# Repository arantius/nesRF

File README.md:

nesRF is a project to retrofit wireless capability into otherwise standard
NES and SNES video game controllers.  It is both hardware (schematic and PCB)
and software (running on an ATMega microcontroller).

The primary goals are:

* Clean design.  External appearance should be minimal, with few visible
  changes from the original stock hardware, besides removing the wire.
* Cross-compatibility: especially, the SNES controller will co-operate with
  either the SNES or NES receiver.

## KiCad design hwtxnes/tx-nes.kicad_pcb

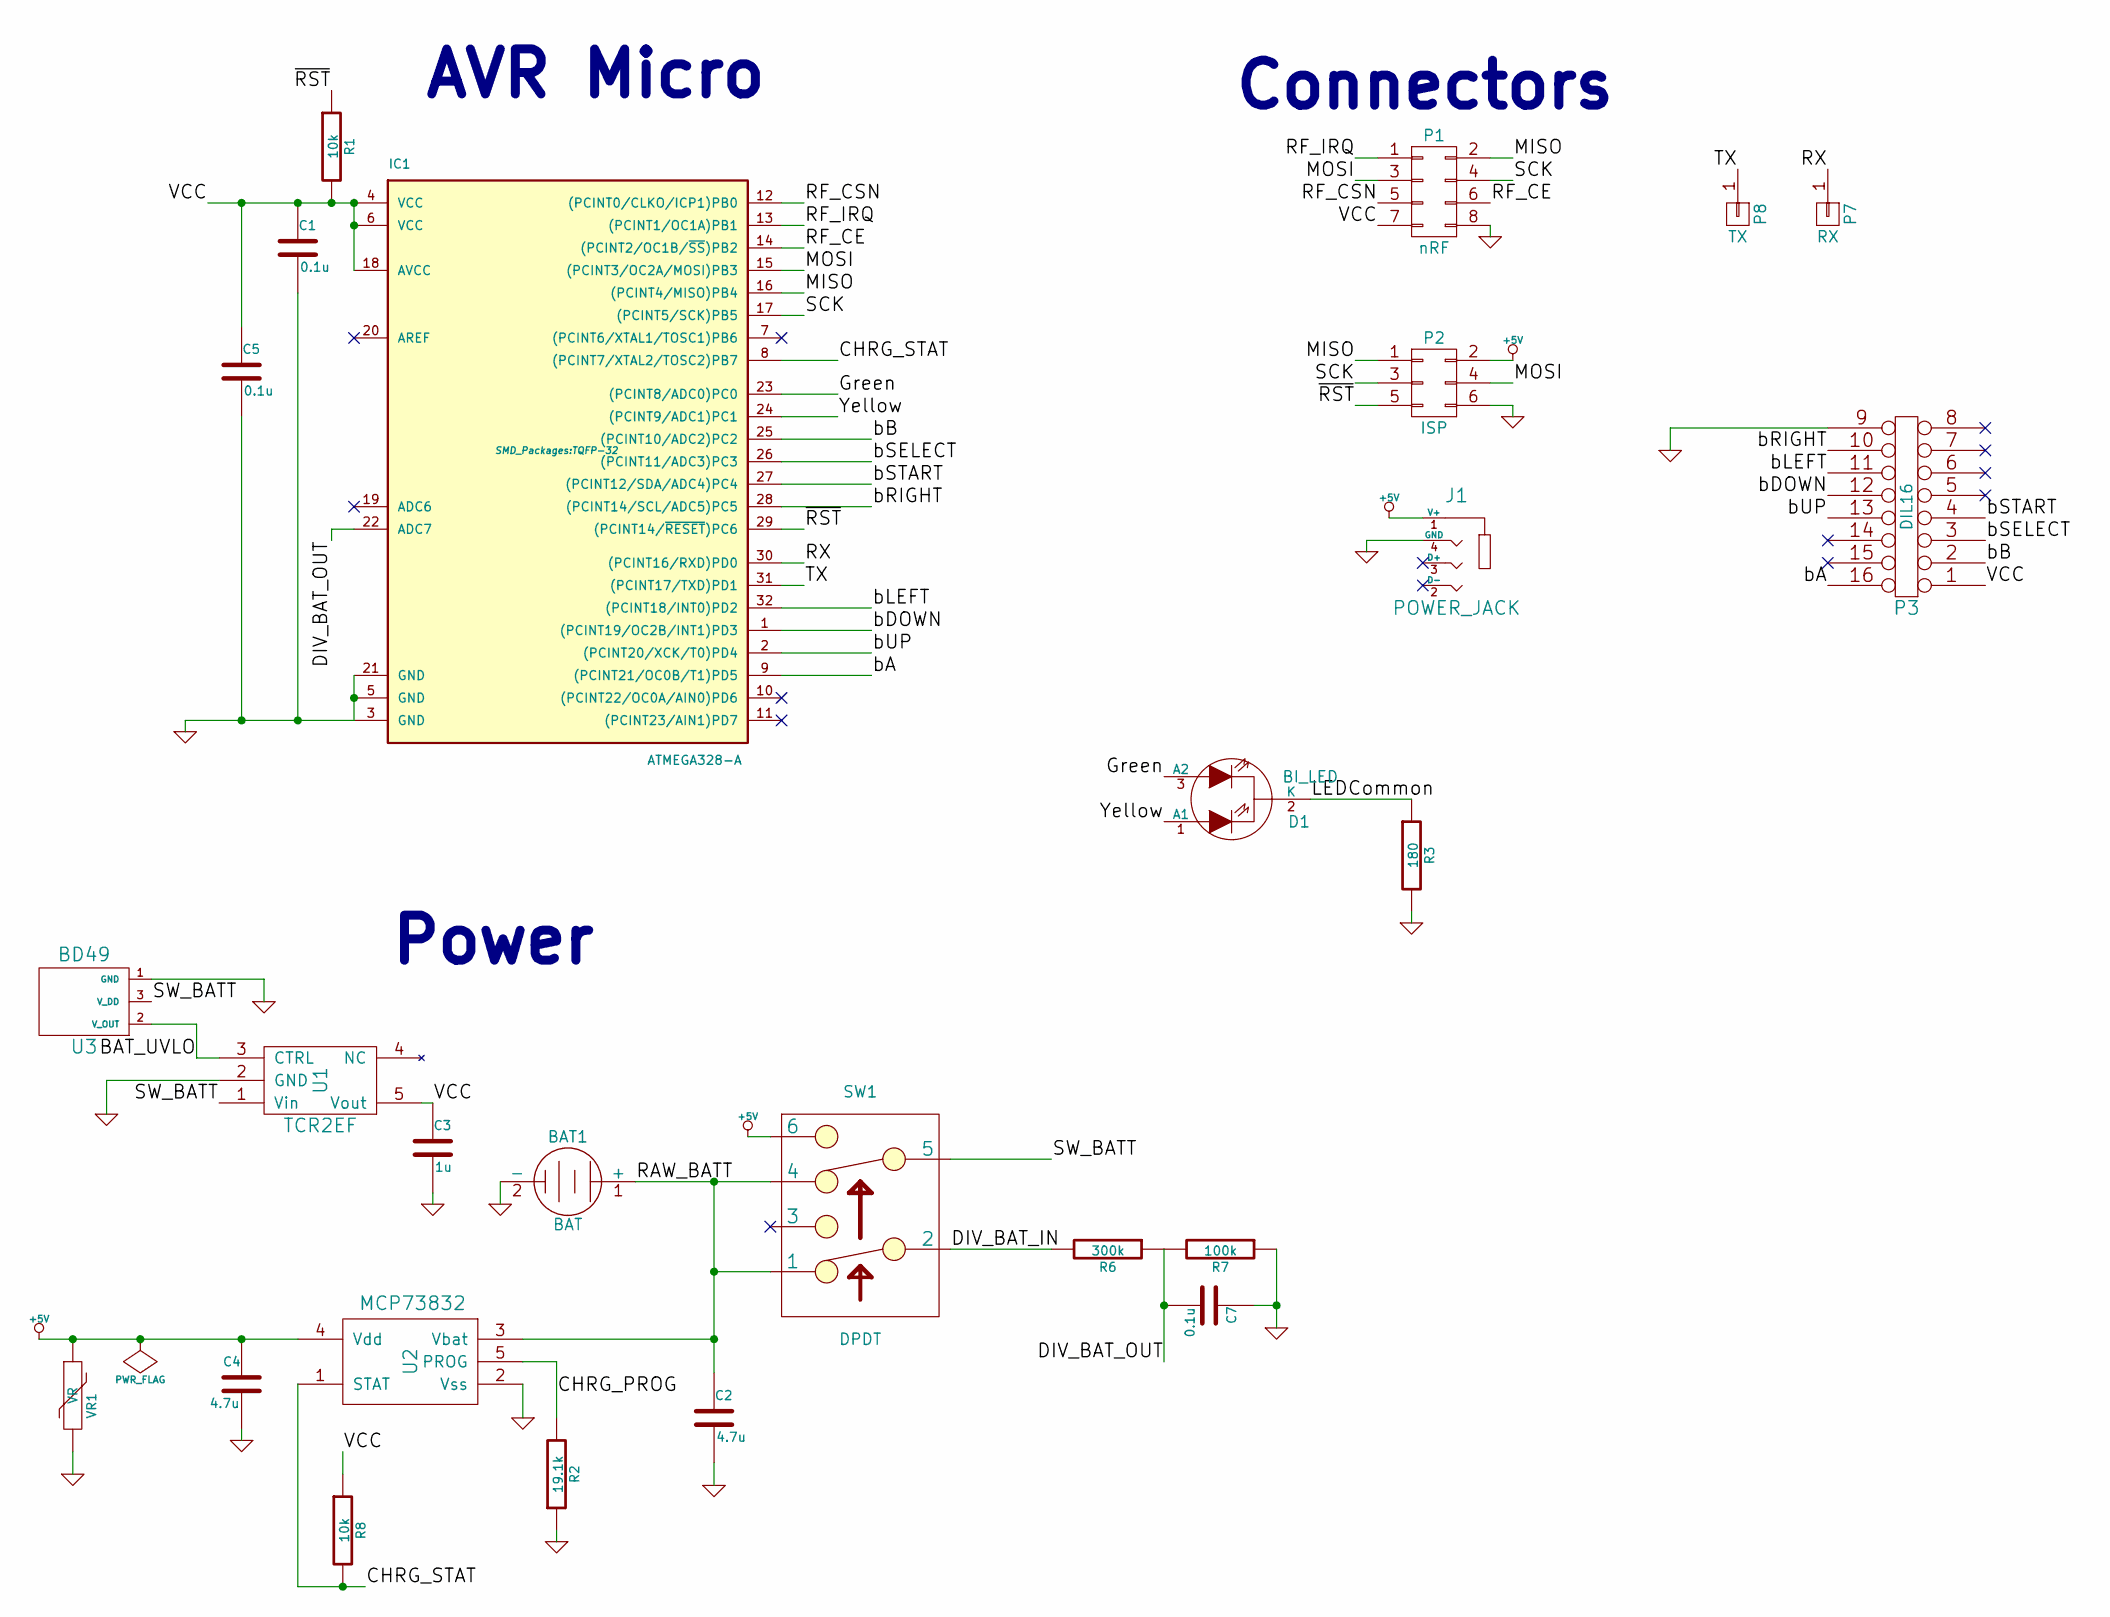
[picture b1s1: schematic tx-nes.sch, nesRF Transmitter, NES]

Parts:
BAT1: BAT; PINHEAD1-2
C1, C5, C7: 0.1u; C_0402
C2, C4: 4.7u; C_0402
C3: 1u; C_0402
D1: BI_LED; Pin_Header_Straight_1x03
IC1: ATMEGA328-A; TQFP-32
J1: POWER_JACK; SJ-4351x
P1: nRF; nRF_Header_2x04
P2: ISP; ISP_POGO
P3: DIL16; NES_PCB_INTERCONNECT
P7: RX; SolderWirePad_single_0-8mmDrill
P8: TX; SolderWirePad_single_0-8mmDrill
R1, R8: 10k; R_0402
R2: 19.1k; R_0402
R3: 180; R_0402
R6: 300k; R_0402
R7: 100k; R_0402
SW1: DPDT; SK22D01
U1: TCR2EF; SOT23-5
U2: MCP73832; SOT23-5
U3: BD49; SSOP-3
VR1: VR; SMD-0603

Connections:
+5V: C4.1, J1.1 (V+), P2.2, SW1.6, U2.4 (Vdd), VR1.1
/BAT_UVLO: U1.3 (CTRL), U3.2 (V_OUT)
/CHRG_PROG: R2.2, U2.5 (PROG)
/CHRG_STAT: IC1.8 ((PCINT7/XTAL2/TOSC2)PB7), R8.2, U2.1 (STAT)
/DIV_BAT_IN: R6.2, SW1.2
/DIV_BAT_OUT: C7.2, IC1.22 (ADC7), R6.1, R7.2
/Green: D1.3 (A2), IC1.23 ((PCINT8/ADC0)PC0)
/LEDCommon: D1.2 (K), R3.1
/MISO: IC1.16 ((PCINT4/MISO)PB4), P1.2, P2.1
/MOSI: IC1.15 ((PCINT3/OC2A/MOSI)PB3), P1.3, P2.4
/RAW_BATT: BAT1.1 (+), C2.1, SW1.1, SW1.4, U2.3 (Vbat)
/RF_CE: IC1.14 ((PCINT2/OC1B/~SS~)PB2), P1.6
/RF_CSN: IC1.12 ((PCINT0/CLKO/ICP1)PB0), P1.5
/RF_IRQ: IC1.13 ((PCINT1/OC1A)PB1), P1.1
/RX: IC1.30 ((PCINT16/RXD)PD0), P7.1
/SCK: IC1.17 ((PCINT5/SCK)PB5), P1.4, P2.3
/SW_BATT: SW1.5, U1.1 (Vin), U3.3 (V_DD)
/TX: IC1.31 ((PCINT17/TXD)PD1), P8.1
/VCC: C1.1, C3.1, C5.1, IC1.4 (VCC), IC1.6 (VCC), IC1.18 (AVCC), P1.7, P3.1, R1.2, R8.1, U1.5 (Vout)
/Yellow: D1.1 (A1), IC1.24 ((PCINT9/ADC1)PC1)
/bA: IC1.9 ((PCINT21/OC0B/T1)PD5), P3.16
/bB: IC1.25 ((PCINT10/ADC2)PC2), P3.2
/bDOWN: IC1.1 ((PCINT19/OC2B/INT1)PD3), P3.12
/bLEFT: IC1.32 ((PCINT18/INT0)PD2), P3.11
/bRIGHT: IC1.28 ((PCINT14/SCL/ADC5)PC5), P3.10
/bSELECT: IC1.26 ((PCINT11/ADC3)PC3), P3.3
/bSTART: IC1.27 ((PCINT12/SDA/ADC4)PC4), P3.4
/bUP: IC1.2 ((PCINT20/XCK/T0)PD4), P3.13
/~RST: IC1.29 ((PCINT14/~RESET~)PC6), P2.5, R1.1
GND: BAT1.2 (-), C1.2, C2.2, C3.2, C4.2, C5.2, C7.1, IC1.3 (GND), IC1.5 (GND), IC1.21 (GND), J1.4 (GND), P1.8, P2.6, P3.9, R2.1, R3.2, R7.1, U1.2 (GND), U2.2 (Vss), U3.1 (GND), VR1.2

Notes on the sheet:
Connectors
AVR Micro
Power

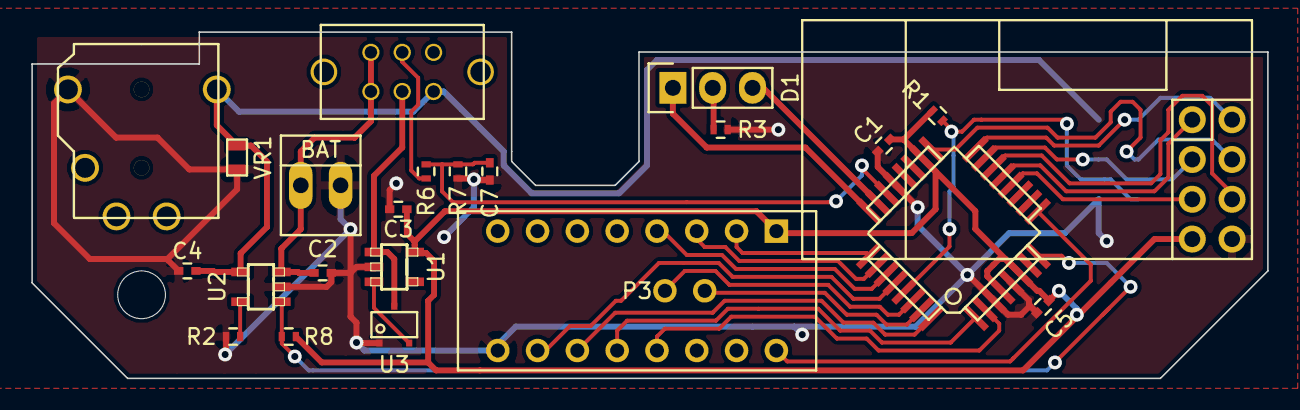
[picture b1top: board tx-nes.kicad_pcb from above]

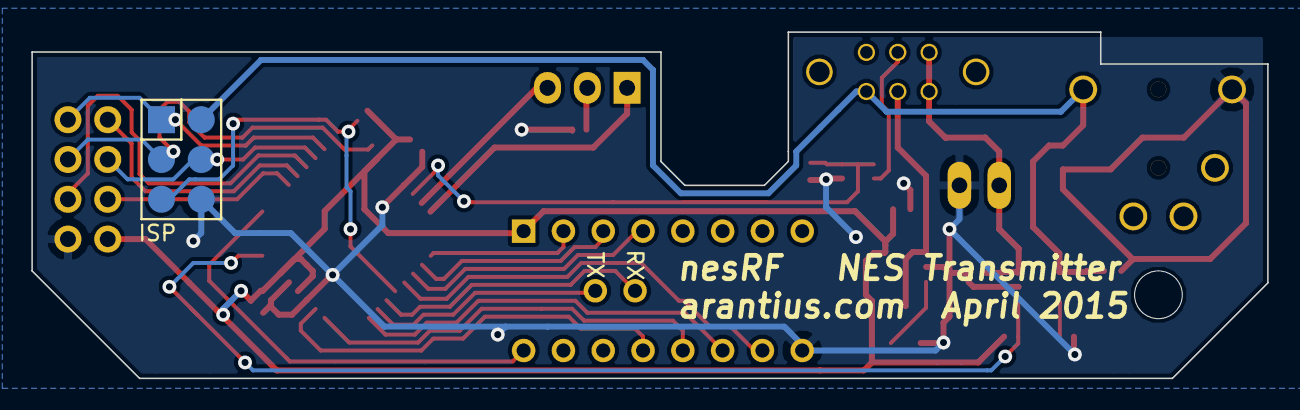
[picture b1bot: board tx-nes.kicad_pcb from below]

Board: 2 copper layers, 78.9 x 22.1 mm, 27 parts (3 on the bottom side), 30 nets.

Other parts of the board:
Mount_Hole: 1pin; NPTH_90

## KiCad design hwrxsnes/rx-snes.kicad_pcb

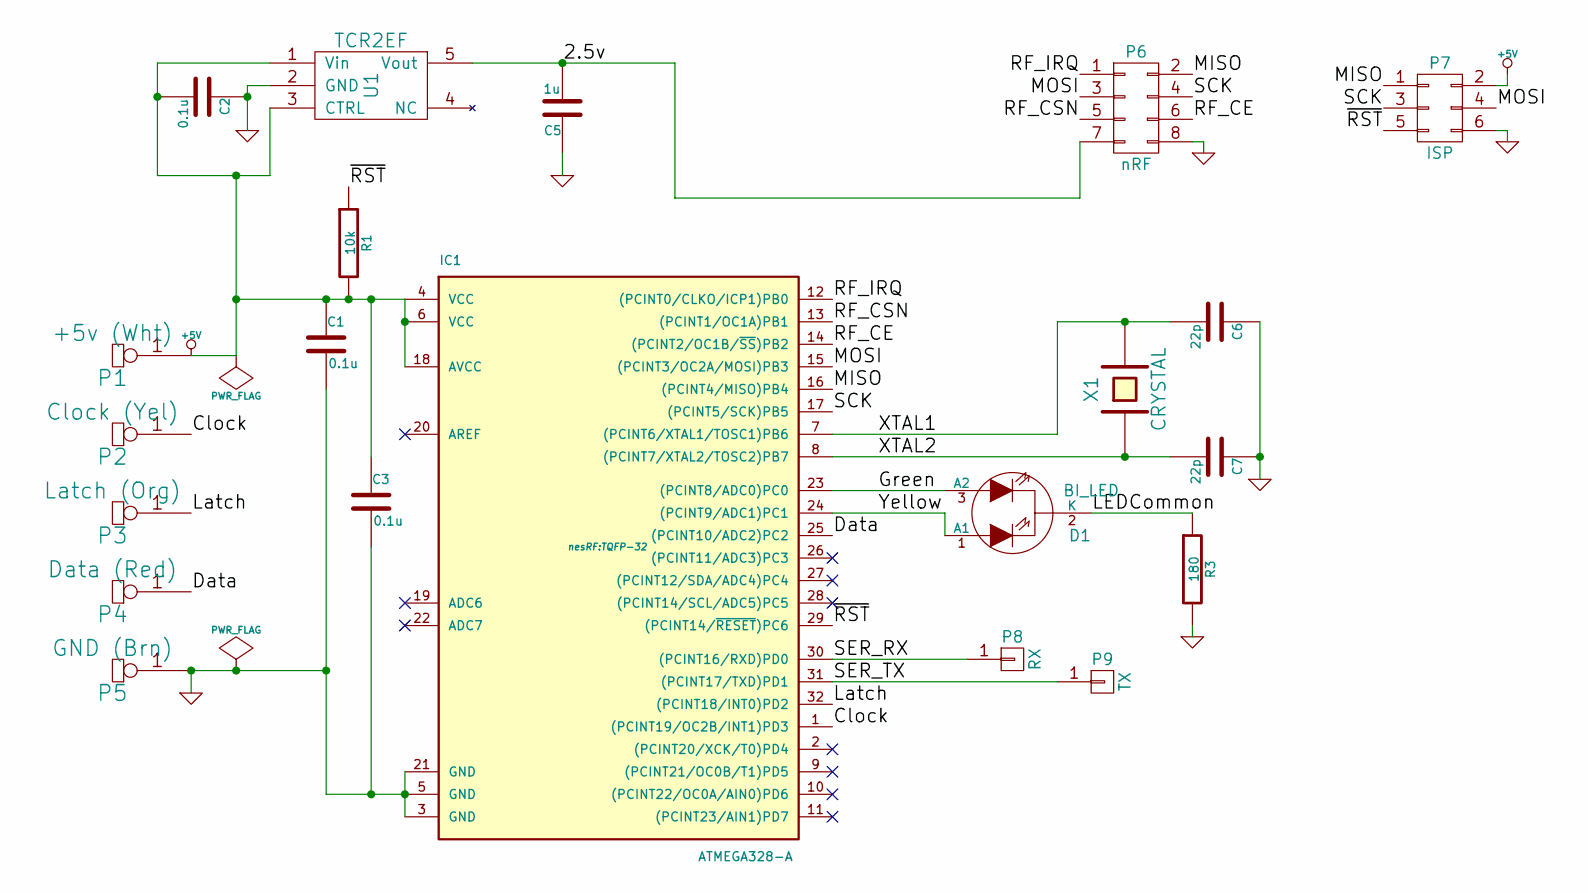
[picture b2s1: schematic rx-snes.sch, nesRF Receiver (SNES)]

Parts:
C1, C2, C3: 0.1u; C_0402
C5: 1u; C_0402
C6, C7: 22p; C_0402
D1: BI_LED; Pin_Header_Straight_1x03
IC1: ATMEGA328-A; TQFP-32
P1: +5v (Wht); Small_1x_Pad
P2: Clock (Yel); Small_1x_Pad
P3: Latch (Org); Small_1x_Pad
P4: Data (Red); Small_1x_Pad
P5: GND (Brn); Small_1x_Pad
P6: nRF; Pin_Header_Straight_2x04
P7: ISP; ISP_POGO
P8: RX; Small_1x_Pad
P9: TX; Small_1x_Pad
R1: 10k; R_0402
R3: 180; R_0402
U1: TCR2EF; SOT23-5
X1: CRYSTAL; TSX-3225

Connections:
+5V: C1.1, C2.2, C3.1, IC1.4 (VCC), IC1.6 (VCC), IC1.18 (AVCC), P1.1, P7.2, R1.2, U1.1 (Vin), U1.3 (CTRL)
/2.5v: C5.2, P6.7, U1.5 (Vout)
/Clock: IC1.1 ((PCINT19/OC2B/INT1)PD3), P2.1
/Data: IC1.25 ((PCINT10/ADC2)PC2), P4.1
/Green: D1.3 (A2), IC1.23 ((PCINT8/ADC0)PC0)
/LEDCommon: D1.2 (K), R3.1
/Latch: IC1.32 ((PCINT18/INT0)PD2), P3.1
/MISO: IC1.16 ((PCINT4/MISO)PB4), P6.2, P7.1
/MOSI: IC1.15 ((PCINT3/OC2A/MOSI)PB3), P6.3, P7.4
/RF_CE: IC1.14 ((PCINT2/OC1B/~SS~)PB2), P6.6
/RF_CSN: IC1.13 ((PCINT1/OC1A)PB1), P6.5
/RF_IRQ: IC1.12 ((PCINT0/CLKO/ICP1)PB0), P6.1
/SCK: IC1.17 ((PCINT5/SCK)PB5), P6.4, P7.3
/SER_RX: IC1.30 ((PCINT16/RXD)PD0), P8.1
/SER_TX: IC1.31 ((PCINT17/TXD)PD1), P9.1
/XTAL1: C6.2, IC1.7 ((PCINT6/XTAL1/TOSC1)PB6), X1.2
/XTAL2: C7.2, IC1.8 ((PCINT7/XTAL2/TOSC2)PB7), X1.1
/Yellow: D1.1 (A1), IC1.24 ((PCINT9/ADC1)PC1)
/~RST: IC1.29 ((PCINT14/~RESET~)PC6), P7.5, R1.1
GND: C1.2, C2.1, C3.2, C5.1, C6.1, C7.1, IC1.3 (GND), IC1.5 (GND), IC1.21 (GND), P5.1, P6.8, P7.6, R3.2, U1.2 (GND)

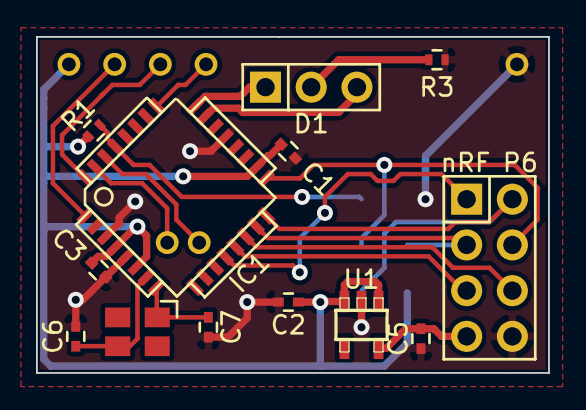
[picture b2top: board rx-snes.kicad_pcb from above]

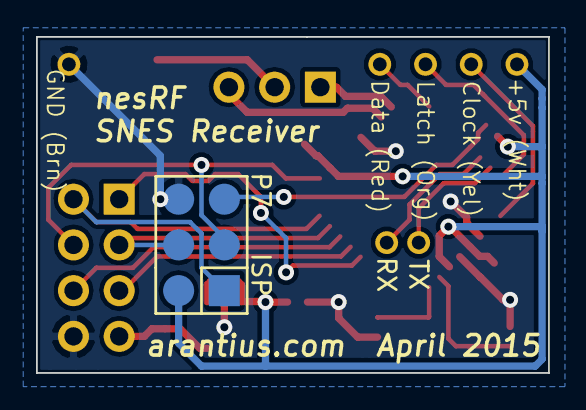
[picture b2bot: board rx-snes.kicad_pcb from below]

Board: 2 copper layers, 28.4 x 18.7 mm, 21 parts (3 on the bottom side), 20 nets.

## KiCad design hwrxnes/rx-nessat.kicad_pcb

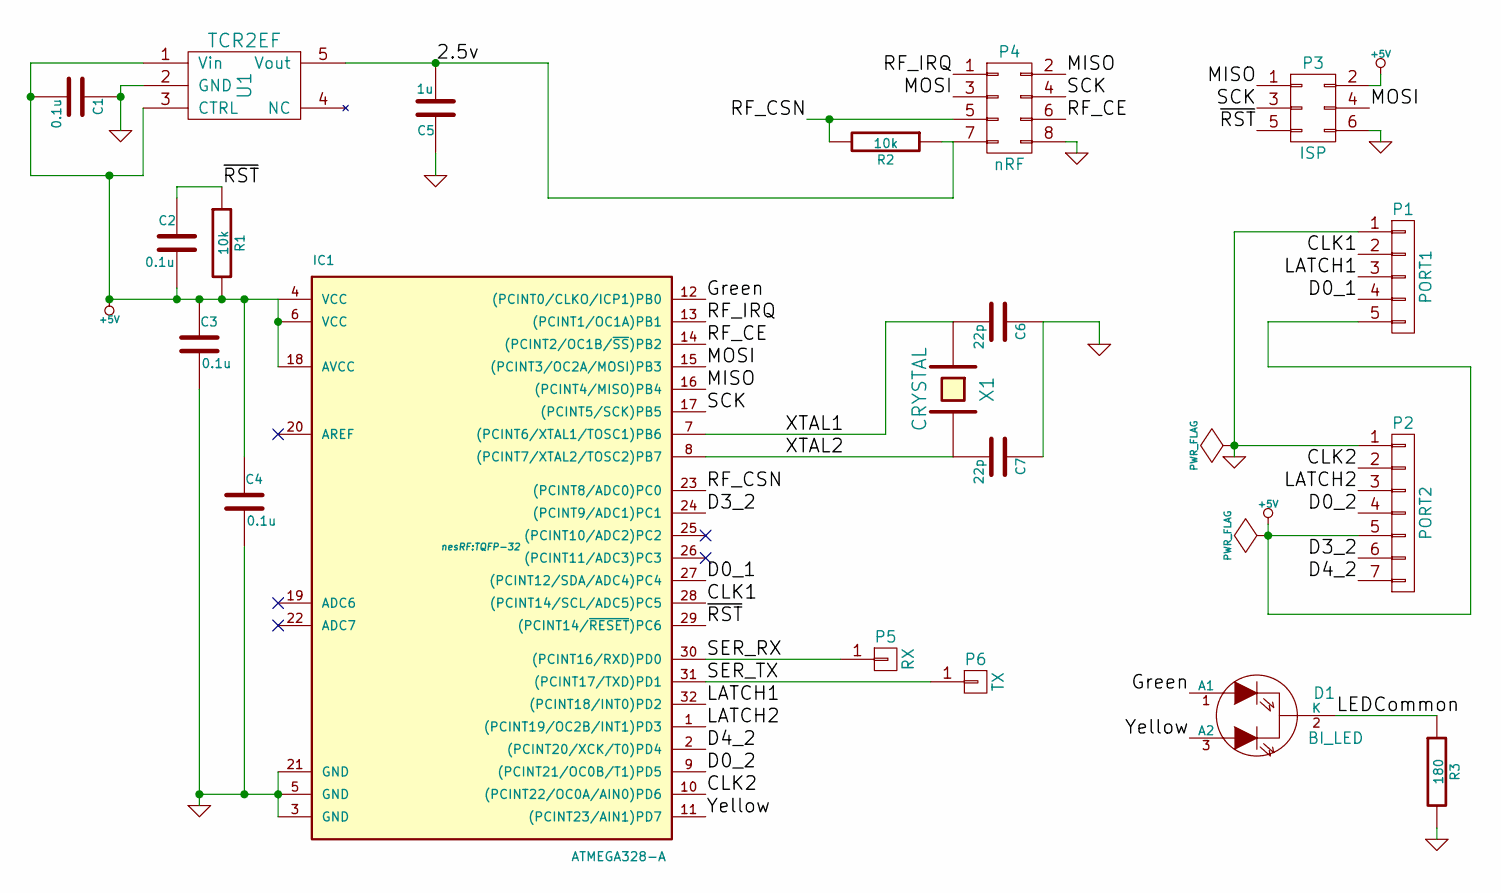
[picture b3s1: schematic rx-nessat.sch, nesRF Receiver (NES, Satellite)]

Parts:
C1, C2, C3, C4: 0.1u; C_0402
C5: 1u; C_0402
C6, C7: 22p; C_0402
D1: BI_LED; Pin_Header_Straight_1x03
IC1: ATMEGA328-A; TQFP-32
P1: PORT1; Pin_Header_Straight_1x05
P2: PORT2; Pin_Header_Straight_1x07
P3: ISP; Pin_Header_Straight_2x03
P4: nRF; nRF_Header_2x04
P5: RX; Small_1x_Pad
P6: TX; Small_1x_Pad
R1, R2: 10k; R_0402
R3: 180; R_0402
U1: TCR2EF; SOT23-5
X1: CRYSTAL; TSX-3225

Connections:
+5V: C1.2, C2.2, C3.1, C4.1, IC1.4 (VCC), IC1.6 (VCC), IC1.18 (AVCC), P1.5, P2.5, P3.2, R1.2, U1.1 (Vin), U1.3 (CTRL)
/2.5v: C5.2, P4.7, R2.1, U1.5 (Vout)
/CLK1: IC1.28 ((PCINT14/SCL/ADC5)PC5), P1.2
/CLK2: IC1.10 ((PCINT22/OC0A/AIN0)PD6), P2.2
/D0_1: IC1.27 ((PCINT12/SDA/ADC4)PC4), P1.4
/D0_2: IC1.9 ((PCINT21/OC0B/T1)PD5), P2.4
/D3_2: IC1.24 ((PCINT9/ADC1)PC1), P2.6
/D4_2: IC1.2 ((PCINT20/XCK/T0)PD4), P2.7
/Green: D1.1 (A1), IC1.12 ((PCINT0/CLKO/ICP1)PB0)
/LATCH1: IC1.32 ((PCINT18/INT0)PD2), P1.3
/LATCH2: IC1.1 ((PCINT19/OC2B/INT1)PD3), P2.3
/LEDCommon: D1.2 (K), R3.1
/MISO: IC1.16 ((PCINT4/MISO)PB4), P3.1, P4.2
/MOSI: IC1.15 ((PCINT3/OC2A/MOSI)PB3), P3.4, P4.3
/RF_CE: IC1.14 ((PCINT2/OC1B/~SS~)PB2), P4.6
/RF_CSN: IC1.23 ((PCINT8/ADC0)PC0), P4.5, R2.2
/RF_IRQ: IC1.13 ((PCINT1/OC1A)PB1), P4.1
/SCK: IC1.17 ((PCINT5/SCK)PB5), P3.3, P4.4
/SER_RX: IC1.30 ((PCINT16/RXD)PD0), P5.1
/SER_TX: IC1.31 ((PCINT17/TXD)PD1), P6.1
/XTAL1: C6.2, IC1.7 ((PCINT6/XTAL1/TOSC1)PB6), X1.1
/XTAL2: C7.2, IC1.8 ((PCINT7/XTAL2/TOSC2)PB7), X1.2
/Yellow: D1.3 (A2), IC1.11 ((PCINT23/AIN1)PD7)
/~RST: C2.1, IC1.29 ((PCINT14/~RESET~)PC6), P3.5, R1.1
GND: C1.1, C3.2, C4.2, C5.1, C6.1, C7.1, IC1.3 (GND), IC1.5 (GND), IC1.21 (GND), P1.1, P2.1, P3.6, P4.8, R3.2, U1.2 (GND)

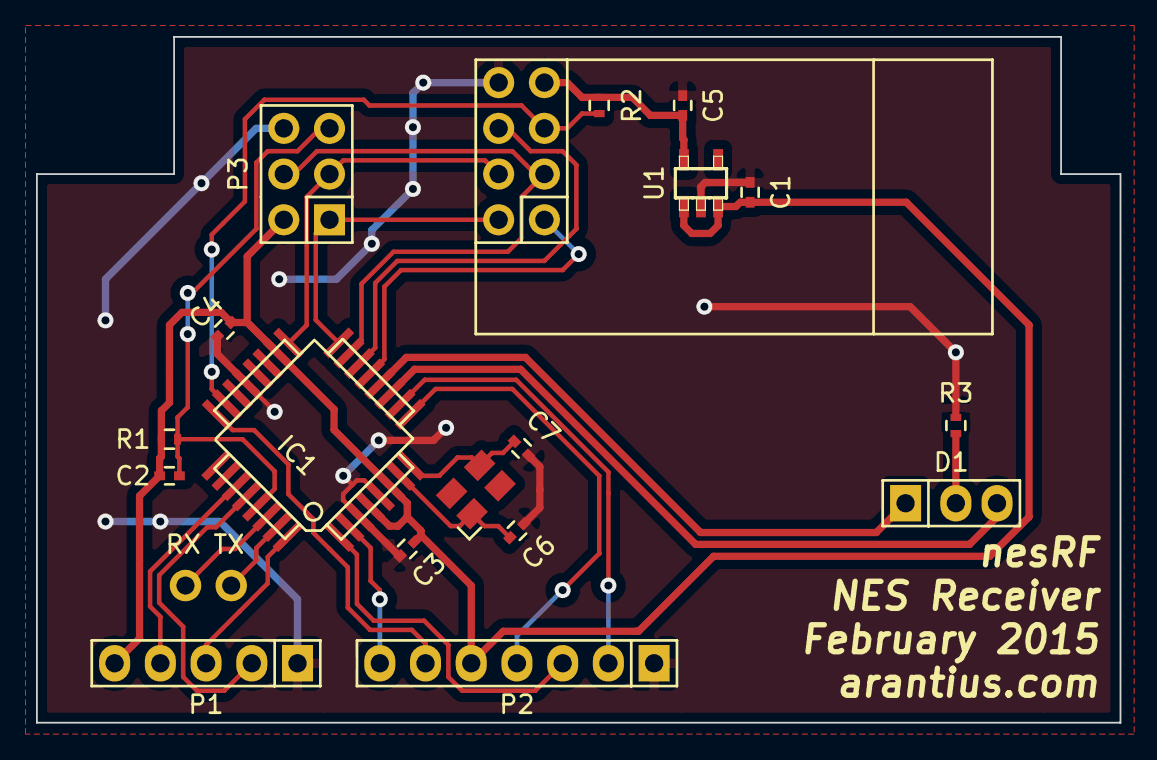
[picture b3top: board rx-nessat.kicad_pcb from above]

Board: 2 copper layers, 60.2 x 38.1 mm, 20 parts (0 on the bottom side), 25 nets.

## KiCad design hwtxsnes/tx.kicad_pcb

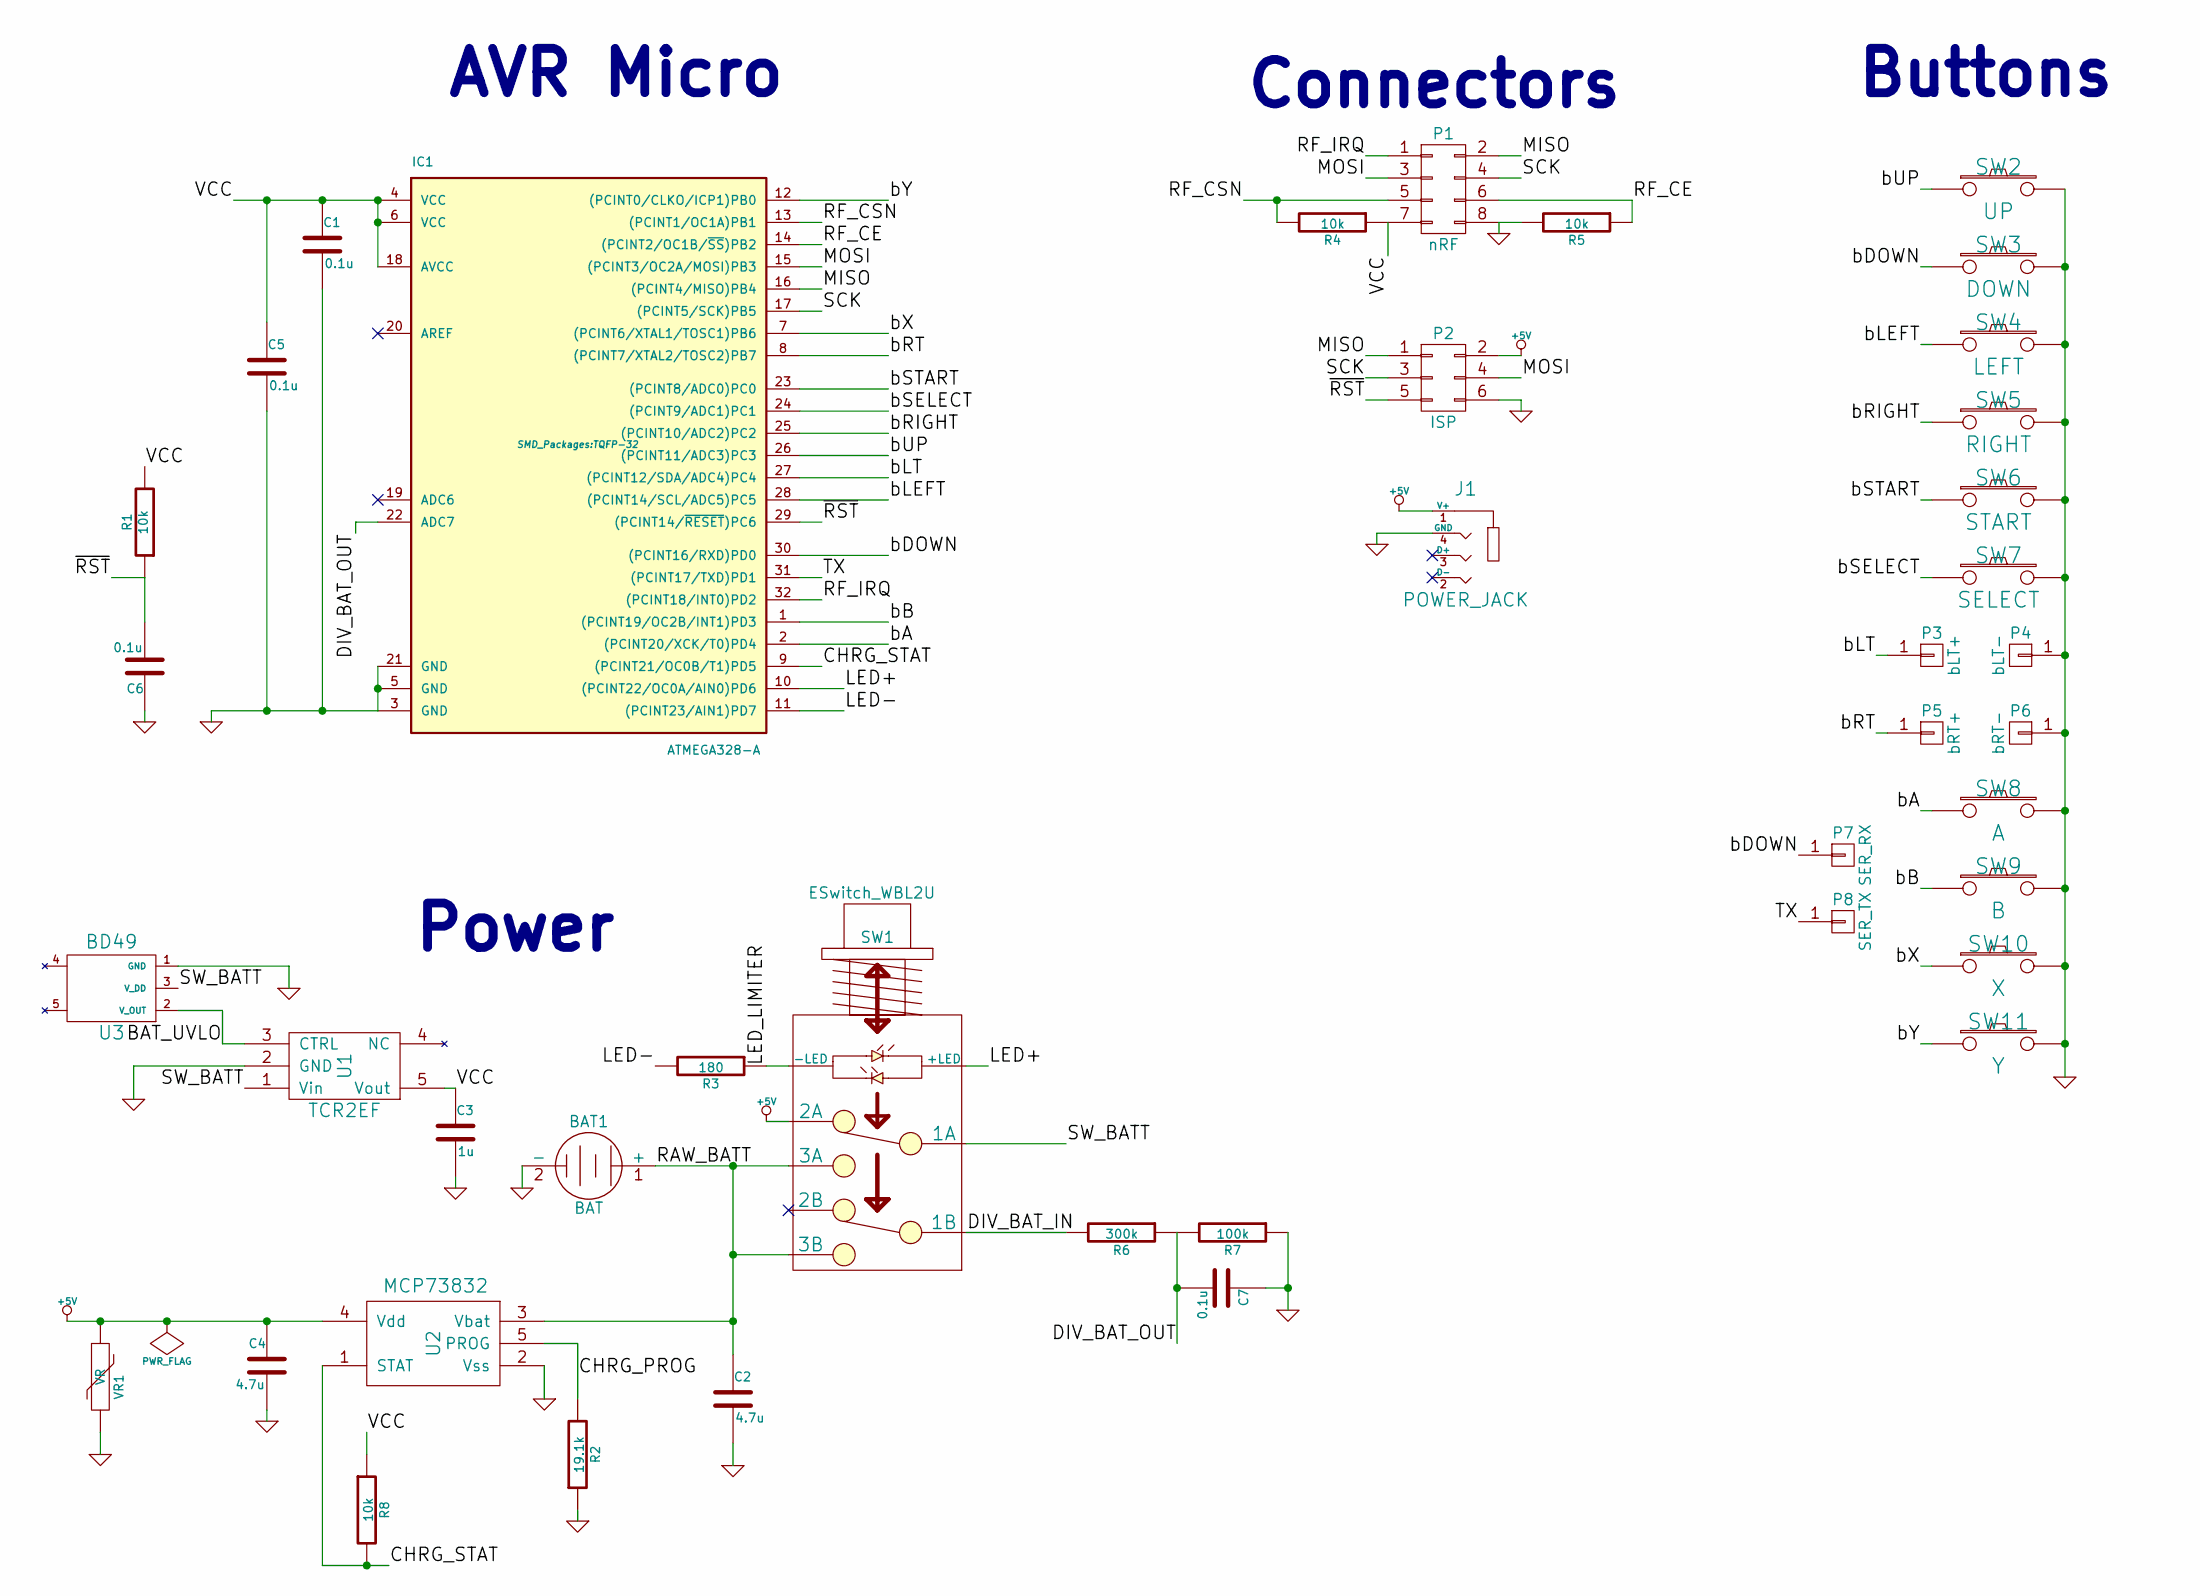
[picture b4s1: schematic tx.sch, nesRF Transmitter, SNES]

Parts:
BAT1: BAT; PINHEAD1-2
C1, C5, C6, C7: 0.1u; SMD-0402_c
C2, C4: 4.7u; SMD-0402_c
C3: 1u; SMD-0402_c
IC1: ATMEGA328-A; TQFP-32
J1: POWER_JACK; SJ-4351x
P1: nRF; nRF_Header_2x04
P2: ISP; Pin_Header_Straight_2x03
P3: bLT+; SolderWirePad_single_0-8mmDrill
P4: bLT-; SolderWirePad_single_0-8mmDrill
P5: bRT+; SolderWirePad_single_0-8mmDrill
P6: bRT-; SolderWirePad_single_0-8mmDrill
P7: SER_RX; SolderWirePad_single_0-8mmDrill
P8: SER_TX; SolderWirePad_single_0-8mmDrill
R1, R4, R5, R8: 10k; SMD-0402_r
R2: 19.1k; SMD-0402_r
R3: 180; SMD-0402_r
R6: 300k; SMD-0402_r
R7: 100k; SMD-0402_r
SW1: ESwitch_WBL2U; Eswitch_WBL_2U
SW2: UP; Carbon_Switch_PCB_Pad
SW3: DOWN; Carbon_Switch_PCB_Pad
SW4: LEFT; Carbon_Switch_PCB_Pad
SW5: RIGHT; Carbon_Switch_PCB_Pad
SW6: START; Carbon_Switch_PCB_Pad
SW7: SELECT; Carbon_Switch_PCB_Pad
SW8: A; Carbon_Switch_PCB_Pad
SW9: B; Carbon_Switch_PCB_Pad
SW10: X; Carbon_Switch_PCB_Pad
SW11: Y; Carbon_Switch_PCB_Pad
U1: TCR2EF; SOT-23-5
U2: MCP73832; SOT-23-5
U3: BD49; SSOP-3
VR1: VR; SMD-0603

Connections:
+5V: C4.1, J1.1 (V+), P2.2, SW1.1 (2A), U2.4 (Vdd), VR1.1
/BAT_UVLO: U1.3 (CTRL), U3.2 (V_OUT)
/CHRG_PROG: R2.2, U2.5 (PROG)
/CHRG_STAT: IC1.9 ((PCINT21/OC0B/T1)PD5), R8.2, U2.1 (STAT)
/DIV_BAT_IN: R6.2, SW1.5 (1B)
/DIV_BAT_OUT: C7.2, IC1.22 (ADC7), R6.1, R7.2
/LED+: IC1.10 ((PCINT22/OC0A/AIN0)PD6), SW1.+ (+LED)
/LED-: IC1.11 ((PCINT23/AIN1)PD7), R3.2
/LED_LIMITER: R3.1, SW1.- (-LED)
/MISO: IC1.16 ((PCINT4/MISO)PB4), P1.2, P2.1
/MOSI: IC1.15 ((PCINT3/OC2A/MOSI)PB3), P1.3, P2.4
/RAW_BATT: BAT1.1 (+), C2.1, SW1.3 (3A), SW1.6 (3B), U2.3 (Vbat)
/RF_CE: IC1.14 ((PCINT2/OC1B/~SS~)PB2), P1.6, R5.1
/RF_CSN: IC1.13 ((PCINT1/OC1A)PB1), P1.5, R4.2
/RF_IRQ: IC1.32 ((PCINT18/INT0)PD2), P1.1
/SCK: IC1.17 ((PCINT5/SCK)PB5), P1.4, P2.3
/SW_BATT: SW1.2 (1A), U1.1 (Vin), U3.3 (V_DD)
/TX: IC1.31 ((PCINT17/TXD)PD1), P8.1
/VCC: C1.1, C3.1, C5.1, IC1.4 (VCC), IC1.6 (VCC), IC1.18 (AVCC), P1.7, R1.2, R4.1, R8.1, U1.5 (Vout)
/bA: IC1.2 ((PCINT20/XCK/T0)PD4), SW8.1
/bB: IC1.1 ((PCINT19/OC2B/INT1)PD3), SW9.1
/bDOWN: IC1.30 ((PCINT16/RXD)PD0), P7.1, SW3.1
/bLEFT: IC1.28 ((PCINT14/SCL/ADC5)PC5), SW4.1
/bLT: IC1.27 ((PCINT12/SDA/ADC4)PC4), P3.1
/bRIGHT: IC1.25 ((PCINT10/ADC2)PC2), SW5.1
/bRT: IC1.8 ((PCINT7/XTAL2/TOSC2)PB7), P5.1
/bSELECT: IC1.24 ((PCINT9/ADC1)PC1), SW7.1
/bSTART: IC1.23 ((PCINT8/ADC0)PC0), SW6.1
/bUP: IC1.26 ((PCINT11/ADC3)PC3), SW2.1
/bX: IC1.7 ((PCINT6/XTAL1/TOSC1)PB6), SW10.1
/bY: IC1.12 ((PCINT0/CLKO/ICP1)PB0), SW11.1
/~RST: C6.2, IC1.29 ((PCINT14/~RESET~)PC6), P2.5, R1.1
GND: BAT1.2 (-), C1.2, C2.2, C3.2, C4.2, C5.2, C6.1, C7.1, IC1.3 (GND), IC1.5 (GND), IC1.21 (GND), J1.4 (GND), P1.8, P2.6, P4.1, P6.1, R2.1, R5.2, R7.1, SW2.2, SW3.2, SW4.2, SW5.2, SW6.2, SW7.2, SW8.2, SW9.2, SW10.2, SW11.2, U1.2 (GND), U2.2 (Vss), U3.1 (GND), VR1.2

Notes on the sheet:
Buttons
Connectors
AVR Micro
Power

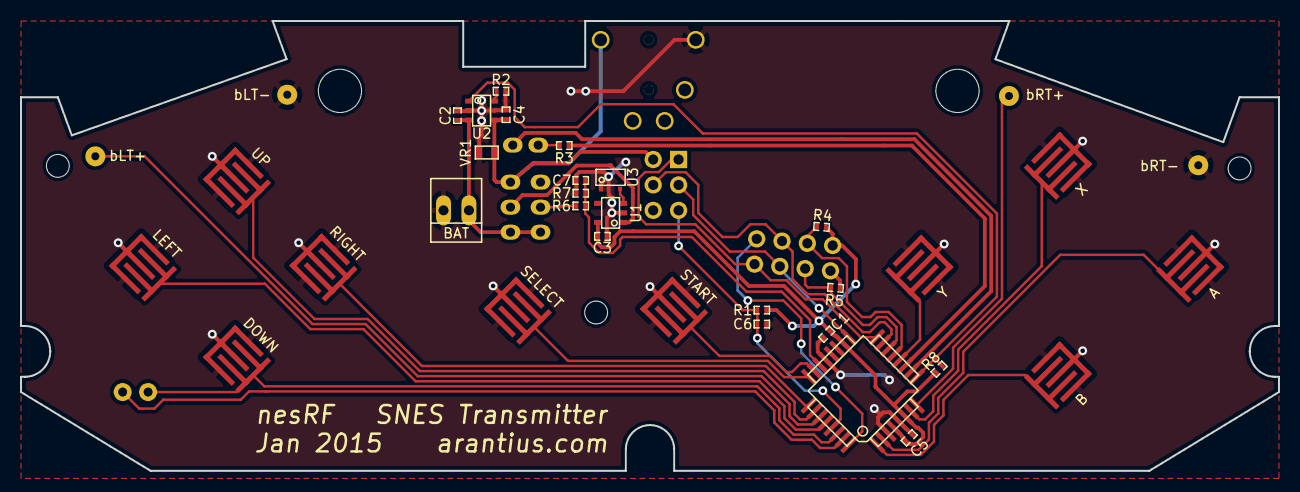
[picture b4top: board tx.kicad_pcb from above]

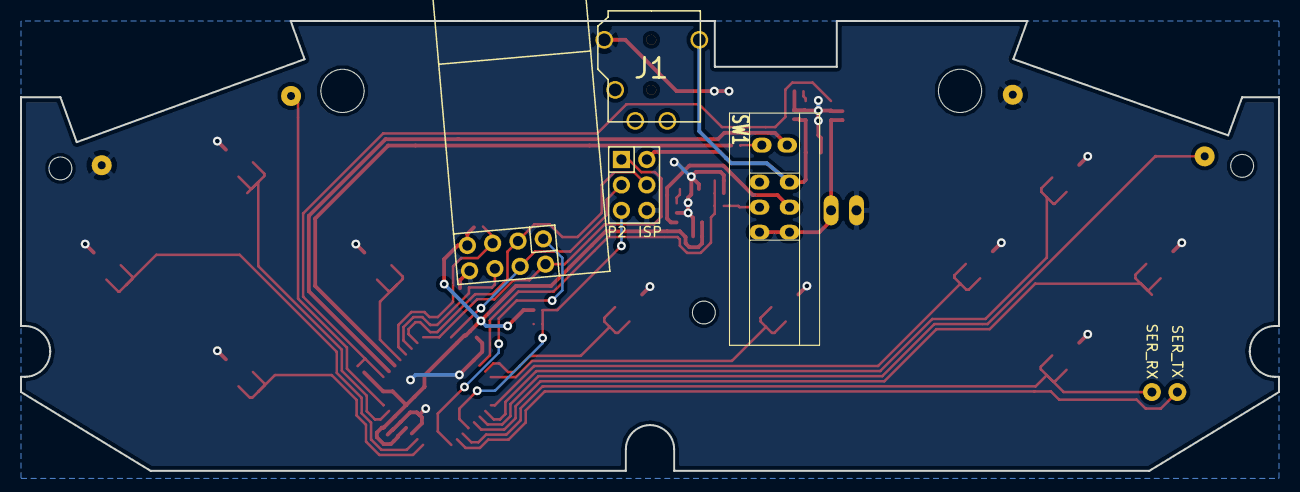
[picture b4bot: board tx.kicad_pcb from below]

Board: 2 copper layers, 125.7 x 45.0 mm, 46 parts (6 on the bottom side), 33 nets.

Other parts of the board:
MH1, MH3, MH5: MHole; MOUNT_HOLE_80
MH2, MH4: MHole; MOUNT_HOLE_170

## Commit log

2015-01-02 initial commit; readme
2015-01-02 Rough implementation of hardware, and RX software.
2015-01-05 v2
    * Schematic revs:
    * TVS protection on TX
    * TX voltage divider moved after the power switch
    * RX adds crystal to run at 16MHz
    RX software tested w/ a real console.
2015-01-27 end-to-end working on breadboard
2015-01-30 finalize TX for SNES
2015-02-18 finalize software changes to match PCB layout
2015-02-22 a few SNES tweaks, add NES/satellite RX
2015-02-22 add license
2015-02-25 rename kicad files to disambiguate nes from snes
2015-02-25 manufacturing tweaks
2015-02-25 routing tweaks
2015-03-22 Slow program fuses.
    Factory default 1MHz needs to go slower.
2015-03-22 High transmit power, more retries.
2015-03-22 Remove old non-typed RX code.
2015-03-22 Disable debug.
2015-03-26 Populate data_nes in the correct order.
2015-03-26 Name latch1; prime data pin correctly.
2015-03-26 Disable debug mode.
2015-03-28 Working NES receiver software.
2015-03-30 NES RX two player support.
2015-04-03 NES Sat RX: Interrupts drive data lines.
    Player 1 and 2 only for now.
2015-04-03 x/y are turbo for a/b
2015-04-03 Light green LED when battery is charged.
2015-04-03 Do not use atomic blocks.
    To cause a problem, the interrupt has to hit between the two STS
    instructions that would write the two bytes to `gRfData`; the latch ISR
    copies that to `data` to mutate. This is exceedingly unlikely, but the
    atomic block causes enough of a delay to be a real problem, more often.
2015-04-03 Add eeprom settings for "player 2".
    The SNES receivers handle one channel each. The one programmed with
    these settings should be plugged into port 2.
2015-04-12 Reroute the SNES RX board.
    Both to add a 16MHz crystal and align the holes for easier wiring.
    Refs #2
2015-04-15 First pass at SNES RX code to match board.
2015-04-17 nes TX as daughter board of original PCB
2015-05-03 add 16mhz fuse settings
2015-05-03 Fix led pin mixup.
2015-05-03 attach correct interrupt; drive correct data port
    also latch data for transmit, in case of RF activity during the transmit
    window
2015-05-04 Holes big enough to fit standard pins.
    The 16 pin interconnect going to the main board has holes that don't
    really fit a standard 0.1" header pin. They fit, only barely with too
    much force. The new size matches the TX/RX holes, which fit the pin
    comfortably.
2015-05-04 Move mounting hole to actual standoff position.
2015-05-04 cutout around power jack
2015-05-05 updated gerbers
2015-05-07 Resistor scaled for the WP59GYW bi-color LED.
2015-05-17 NES transmitter software support.
